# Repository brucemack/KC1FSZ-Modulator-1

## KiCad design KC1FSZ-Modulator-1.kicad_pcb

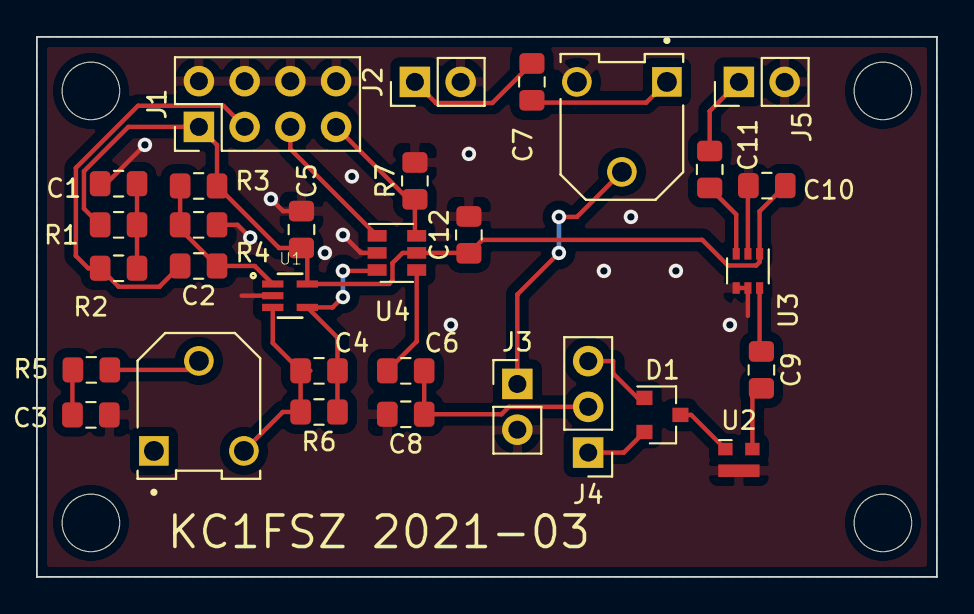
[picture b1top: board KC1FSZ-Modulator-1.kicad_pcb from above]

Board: 2 copper layers, 50.0 x 30.0 mm, 35 parts (0 on the bottom side), 23 nets.

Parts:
C1, C5, C8, C9, C10, C12: 0.1U; C_0805_2012Metric_Pad1.15x1.40mm_HandSolder
C2: 0.01U; C_0805_2012Metric_Pad1.15x1.40mm_HandSolder
C3: 1U; C_0805_2012Metric_Pad1.15x1.40mm_HandSolder
C4: 100P; C_0805_2012Metric_Pad1.15x1.40mm_HandSolder
C6, C7, C11: C; C_0805_2012Metric_Pad1.15x1.40mm_HandSolder
D1: BAT54S; SOT-23
H1, H2, H3, H4: MountingHole; MountingHole_3.2mm_M3_ISO14580
J1: Conn_02x04_Odd_Even; PinHeader_2x04_P2.54mm_Vertical
J2, J3, J5: Conn_01x02; PinHeader_1x02_P2.54mm_Vertical
J4: Conn_01x03; PinHeader_1x03_P2.54mm_Vertical
R1, R2: 2K; R_0805_2012Metric_Pad1.15x1.40mm_HandSolder
R3, R4: 1M; R_0805_2012Metric_Pad1.15x1.40mm_HandSolder
R5: 10K; R_0805_2012Metric_Pad1.15x1.40mm_HandSolder
R6: 100K; R_0805_2012Metric_Pad1.15x1.40mm_HandSolder
R7: R; R_0805_2012Metric_Pad1.15x1.40mm_HandSolder
RV1: 100 (3362W); TRIM_3306F-1-101
RV2: R_POT; TRIM_3306F-1-101
U1: MAX4466EXK; SOT65P210X110-5N
U2: PAT1220-C-6DB; RF_Attenuator_Susumu_PAT1220
U3: BGA2867; SOT-363_SC-70-6
U4: TS5A3159ADBVR; SOT-23-6

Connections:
+5VA: C5.1, C10.1, C12.1, J1.1, R1.1, R3.1, U1.5, U3.1, U4.5
AUDIO_SEL: J1.7, R7.1, U4.6
BFO_IN: C7.1, J2.1
GNDA: C1.2, C3.2, C5.2, C8.2, C10.2, C12.2, J1.2, J1.4, J1.6, J1.8, J2.2, J3.2, J5.2, R4.2, R7.2, RV1.3, U1.2, U2.3, U3.2, U3.4, U3.5, U4.2
IF_OUT: C11.1, J5.1
LINE_IN: J1.5, U4.1
MIC_IN: C2.2, J1.3, R2.2
unnamed: C1.1, R1.2, R2.1
unnamed: C2.1, R3.2, R4.1, U1.1
unnamed: C3.1, R5.2
unnamed: C4.1, R6.1, U1.4, U4.3
unnamed: C4.2, R6.2, RV2.3, U1.3
unnamed: C6.1, C8.1, J4.2
unnamed: C6.2, U4.4
unnamed: C7.2, RV1.1
unnamed: C9.1, U3.6
unnamed: C9.2, U2.2
unnamed: C11.2, U3.3
unnamed: D1.1, J4.3
unnamed: D1.2, J4.1
unnamed: D1.3, U2.1
unnamed: J3.1, RV1.2
unnamed: R5.1, RV2.2

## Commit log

2021-03-24 Working
2021-03-24 Ready for RIT
